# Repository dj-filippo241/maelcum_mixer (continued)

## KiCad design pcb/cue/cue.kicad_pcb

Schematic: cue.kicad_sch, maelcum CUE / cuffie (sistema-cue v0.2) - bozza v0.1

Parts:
C1, C4: 220u 35V; CP_Radial_D8.0mm_P3.50mm
C2, C5: 10u 35V; CP_Radial_D5.0mm_P2.00mm
C3, C6: 1000u 25V; CP_Radial_D10.0mm_P5.00mm
C7, C12: 47u 35V; CP_Radial_D6.3mm_P2.50mm
C8, C11, C13, C16: 10u 25V; C_1206_3216Metric
C9, C10, C14, C15: 4u7 25V; C_1206_3216Metric
C17, C18, C21, C22: 10p C0G; C_0805_2012Metric
C19, C20, C23, C24, C25, C26, C27, C28, C31, C32, C33, C34, C37, C38, C40, C42: 100n; C_0805_2012Metric
C29, C35: 330p C0G; C_0805_2012Metric
C30, C36: 1u film; C_Rect_L7.2mm_W3.5mm_P5.00mm_FKS2_FKP2_MKS2_MKP2
C39: 47u 10V; CP_Radial_D5.0mm_P2.00mm
C41: 2u2 X7R; C_1206_3216Metric
D1, D3, D5: 1N4148W; D_SOD-123
D2, D4: S1G; D_SMA
D6, D7, D8: BAT54W; SOT-323_SC-70
FB1, FB2: ferrite 600R 2A; L_1206_3216Metric
FB3, FB4: ferrite 600R; L_1206_3216Metric
H1, H2: CHASSIS; MountingHole_3.2mm_M3_Pad
J1: C96 maschio; DIN41612_C_3x32_Male_Horizontal_THT
J2: 2x7 cavo piatto; PinHeader_2x07_P2.54mm_Vertical
J3: 2x3 cavo; PinHeader_2x03_P2.54mm_Vertical
K1, K2: G6K-2F DC5; Relay_DPDT_Omron_G6K-2F
Q1, Q6, Q8, Q13: BC847B; SOT-23
Q2, Q3, Q9, Q10: BF245B; TO-92_Inline_Wide
Q4, Q11: MJE340; TO-126-3_Vertical
Q5, Q12: MJE350; TO-126-3_Vertical
Q7, Q14: BC857B; SOT-23
Q15: AO3400A; SOT-23
R1, R3, R5, R8: 120 1%; R_0805_2012Metric
R2, R4: 1k62 1%; R_0805_2012Metric
R6, R9: 1k47 1%; R_0805_2012Metric
R7, R10: 150k 0.1%; R_0805_2012Metric
R11, R12, R13, R14, R15, R16, R17, R18, R19, R20: 10k 0.1%; R_0805_2012Metric
R21, R22, R23, R24: 20k 0.1%; R_0805_2012Metric
R25, R26, R27, R40: 1M; R_0805_2012Metric
R28, R41: 470 1%; R_0805_2012Metric
R29, R30, R31, R42, R43, R44: 1k 1%; R_0805_2012Metric
R32, R33, R45, R46: 22; R_0805_2012Metric
R34, R35, R47, R48: 6.8 1%; R_1206_3216Metric
R36, R37, R49, R50, R53: 100; R_0805_2012Metric
R38, R39, R51, R52: 10 2W; R_Axial_DIN0414_L11.9mm_D4.5mm_P15.24mm_Horizontal
R54: 0; R_1206_3216Metric
R55: 1k; R_0805_2012Metric
R56, R58: 160k 1%; R_0805_2012Metric
R57: 27k4 1%; R_0805_2012Metric
R59: 22k6 1%; R_0805_2012Metric
R60: 15k 1%; R_0805_2012Metric
R61, R62, R64: 10k 1%; R_0805_2012Metric
R63: 120k 1%; R_0805_2012Metric
R65: 140k 1%; R_0805_2012Metric
R66, R68: 10k; R_0805_2012Metric
R67: 1M2 1%; R_0805_2012Metric
RV1, RV2: 500; Potentiometer_Bourns_3266W_Vertical
U1, U2, U3, U4, U8: OPA1612AIDR; SOIC-8_3.9x4.9mm_P1.27mm
U5: TL431; SOT-23
U6, U7: LM339; SOIC-14_3.9x8.7mm_P1.27mm
U40: LM317; TO-220-3_Vertical
U41: LM337; TO-220-3_Vertical
U42: LM317; SOT-223-3_TabPin2
U43: LM337; SOT-223-3_TabPin2
U44: LT3045EMSE; MSOP-12-1EP_3x4.039mm_P0.65mm_EP1.651x2.845mm
U45: LT3094EMSE; MSOP-12-1EP_3x4.039mm_P0.65mm_EP1.651x2.845mm

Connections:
+5V: C39.1, C40.1, C42.1, D5.1 (K), J1.a21, J1.a22, K1.1, K2.1, R55.1, R66.2, R68.2, U6.3 (V+), U7.3 (V+)
+15LN: C11.1, C19.1, C23.1, C25.1, U1.8 (V+), U2.8 (V+), U3.8 (V+), U44.10 (OUTS), U44.11 (OUT), U44.12 (OUT)
+16V5: C8.1, C10.1, R5.1, U42.2 (VO), U44.1 (IN), U44.2 (IN), U44.3 (IN), U44.4 (EN/UV), U44.7 (PGFB)
+18V: C3.1, C27.1, C31.1, C33.1, C37.1, D1.1 (K), D2.2 (A), Q2.3 (D), Q4.2 (C), Q9.3 (D), Q11.2 (C), R1.1, U4.8 (V+), U8.8 (V+), U40.2 (VO)
-15LN: C16.2, C20.2, C24.2, C26.2, U1.4 (V-), U2.4 (V-), U3.4 (V-), U45.10 (OUTS), U45.11 (OUT), U45.12 (OUT)
-16V5: C13.2, C15.2, R8.1, U43.3 (VO), U45.1 (IN), U45.2 (IN), U45.3 (EN/UV), U45.5 (PGFB), U45.13 (IN)
-18V: C6.2, C28.2, C32.2, C34.2, C38.2, D3.2 (A), D4.1 (K), Q3.1 (G), Q3.2 (S), Q5.2 (C), Q10.1 (G), Q10.2 (S), Q12.2 (C), R3.1, U4.4 (V-), U8.4 (V-), U41.3 (VO)
ADJ16+: R5.2, R6.1, U42.1 (ADJ)
ADJ16-: R8.2, R9.1, U43.1 (ADJ)
ADJ18+: C2.1, D1.2 (A), R1.2, R2.1, U40.1 (ADJ)
ADJ18-: C5.2, D3.1 (K), R3.2, R4.1, U41.1 (ADJ)
AGND: C1.2, C2.2, C3.2, C4.1, C5.1, C6.1, C7.2, C8.2, C9.2, C10.2, C11.2, C12.1, C13.1, C14.1, C15.1, C16.1, C19.2, C20.1, C23.2, C24.1, C25.2, C26.1, C27.2, C28.1, C31.2, C32.1, C33.2, C34.1, C37.2, C38.1, J1.a13, J1.a14, J1.a15, J1.a16, J1.a17, J1.a18, J1.a19, J1.a20, J1.b3, J1.b6, J1.b9, J1.b12, J1.b15, J2.2, J2.6, J2.9, J2.13, R2.2, R4.2, R6.2, R7.2, R9.2, R10.2, R25.2, R26.2, R27.2, R40.2, R54.2, U1.3 (+), U1.5 (+), U2.3 (+), U2.5 (+), U4.5 (+), U8.5 (+), U44.6 (ILIM), U44.9 (GND), U44.13 (GND), U45.6 (ILIM), U45.9 (GND)
BLB_L: J2.5, U3.1, U3.2 (-)
BLB_R: J2.12, U3.6 (-), U3.7
BLN_L: Q6.1 (B), R36.2
BLN_R: Q13.1 (B), R49.2
BLP_L: Q7.1 (B), R37.2
BLP_R: Q14.1 (B), R50.2
BL_L: J2.4, R25.1, U3.3 (+)
BL_R: J2.11, R26.1, U3.5 (+)
BN_L: Q4.3 (B), R32.2
BN_R: Q11.3 (B), R45.2
BP_L: Q5.3 (B), R33.2
BP_R: Q12.3 (B), R46.2
CHASSIS: H1.1, H2.1, J1.a25, J1.a26
CS_L: C17.2, J2.1, R15.2, U1.1
CS_R: C18.2, J2.8, R20.2, U1.7
CT: C41.1, D8.1 (A), R67.2, U7.9 (+)
CTRL_GND: C39.2, C40.2, C41.2, C42.2, D6.1 (A), D7.1 (A), J1.a23, J1.a24, J1.c16, J1.c20, J1.c24, J1.c28, Q15.2 (S), R57.2, R59.2, R61.2, U5.3 (A), U6.12 (V-), U7.5 (+), U7.7 (+), U7.11 (+), U7.12 (V-)
CUE1_L: J1.b1, R11.1
CUE1_R: J1.b2, R16.1
CUE2_L: J1.b4, R12.1
CUE2_R: J1.b5, R17.1
CUE3_L: J1.b7, R13.1
CUE3_R: J1.b8, R18.1
CUE4_L: J1.b10, R14.1
CUE4_R: J1.b11, R19.1
D22: R56.2, R57.1, U6.7 (+)
D27: R58.2, R59.1, U6.5 (+)
EN_L: Q4.1 (E), R34.1, R36.1
EN_R: Q11.1 (E), R47.1, R49.1
EP_L: Q5.1 (E), R35.1, R37.1
EP_R: Q12.1 (E), R48.1, R50.1
FB_L: C29.2, R28.2, U4.2 (-)
FB_R: C35.2, R41.2, U8.2 (-)
HP1_R: J3.3, K1.5
HP1_T: J3.1, K1.4
HP2_R: J3.6, K2.5
HP2_T: J3.4, K2.4
HPG: J3.2, J3.5, R54.1
KD: D5.2 (A), K1.8, K2.8, Q15.3 (D)
KG: Q15.1 (G), R53.2
KG0: R53.1, R68.1, U7.14
LV_L: J2.7, R27.1, U4.3 (+)
LV_R: J2.14, R40.1, U8.3 (+)
MB_L: C21.2, J2.3, R22.2, U2.1
MB_R: C22.2, J2.10, R24.2, U2.7
MON_L: J1.b13, R21.1
MON_R: J1.b14, R23.1
N22: D6.3 (K), R62.2, R63.1, U6.8 (-)
N27: D7.3 (K), R64.2, R65.1, U6.10 (-)
NB_L: C30.2, Q1.2 (E), Q3.3 (D), Q7.3 (C), R29.2, R31.2, R33.1
NB_R: C36.2, Q8.2 (E), Q10.3 (D), Q14.3 (C), R42.2, R44.2, R46.1
NMB_L: C21.1, R21.2, R22.1, U2.2 (-)
NMB_R: C22.1, R23.2, R24.1, U2.6 (-)
NS_L: C17.1, R11.2, R12.2, R13.2, R14.2, R15.1, U1.2 (-)
NS_R: C18.1, R16.2, R17.2, R18.2, R19.2, R20.1, U1.6 (-)
NU_L: U4.6 (-), U4.7
NU_R: U8.6 (-), U8.7
OUTA_L: Q6.2 (E), Q7.2 (E), R28.1, R34.2, R35.2, R38.1, R39.1
OUTA_R: Q13.2 (E), Q14.2 (E), R41.1, R47.2, R48.2, R51.1, R52.1
PB_L: C30.1, Q1.3 (C), Q2.1 (G), Q2.2 (S), Q6.3 (C), R30.1, R32.1
PB_R: C36.1, Q8.3 (C), Q9.1 (G), Q9.2 (S), Q13.3 (C), R43.1, R45.1
RAW+22: FB3.1, J1.a5, J1.a6, R56.1
RAW+27: FB1.1, J1.a1, J1.a2, R58.1
RAW-22: FB4.1, J1.a7, J1.a8, R63.2
RAW-27: FB2.1, J1.a3, J1.a4, R65.2
ROK: D8.3 (K), R66.1, R67.1, U6.1, U6.2, U6.13, U6.14
RS1_L: K1.3, R38.2
RS1_R: K1.6, R51.2
RS2_L: K2.3, R39.2
RS2_R: K2.6, R52.2
RT_L: R30.2, RV1.1
RT_R: R43.2, RV2.1
SETN: C14.2, R10.1, U45.8 (SET)
SETP: C9.1, R7.1, U44.8 (SET)
TAP_L: Q1.1 (B), R31.1, RV1.2, RV1.3
TAP_R: Q8.1 (B), R44.1, RV2.2, RV2.3
THN: R60.2, R61.1, U6.9 (+), U6.11 (+)
UO_L: C29.1, R29.1, U4.1
UO_R: C35.1, R42.1, U8.1
V22F+: C7.1, FB3.2, U42.3 (VI)
V22F-: C12.2, FB4.2, U43.2 (VI)
V27F+: C1.1, D2.1 (K), FB1.2, U40.3 (VI)
V27F-: C4.2, D4.2 (A), FB2.2, U41.2 (VI)
VREF: R55.2, R60.1, R62.1, R64.1, U5.1 (K), U5.2 (REF), U6.4 (-), U6.6 (-), U7.4 (-), U7.6 (-), U7.8 (-), U7.10 (-)

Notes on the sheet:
BACKPLANE C96 (classe CUE: slot 1-4 = CUE1-4 in, slot 5 = MON in)
ALIMENTAZIONE +18 audio (LM317 dal raw +27, bulk 1000 uF)
ALIMENTAZIONE -18 audio (LM337 dal raw -27, bulk 1000 uF)
ALIMENTAZIONE +15 LN (LM317 a +16,5 dal raw +22, poi LT3045)
ALIMENTAZIONE -15 LN (LM337 a -16,5 dal raw -22, poi LT3094)
[A] CUE SUMMING L/R (massa virtuale, Rf 10k, -1) e [B] MON (invertente 20k/20k, F4)
[C2] buffer fra BLEND e LEVEL (NOTA: tiene la law del blend esatta)
[E] AMPLI CUFFIA L (OPA1612 + diamond MJE340/350, v0.2)
[F] RSERIE L (10 ohm 2 W, una per jack)
[E] AMPLI CUFFIA R (OPA1612 + diamond MJE340/350, v0.2)
[F] RSERIE R (10 ohm 2 W, una per jack)
[F] RELE' delle cuffie (G6K-2F, 5 V, 237 ohm; eccitati = suono; failsafe)
[G] PROTEZIONE: finestre sui raw +-22 e +-27, timer 1,8 s (il CUE non ascolta c9)
CAVI verso la scheda comandi: J2 pot, J3 cuffie

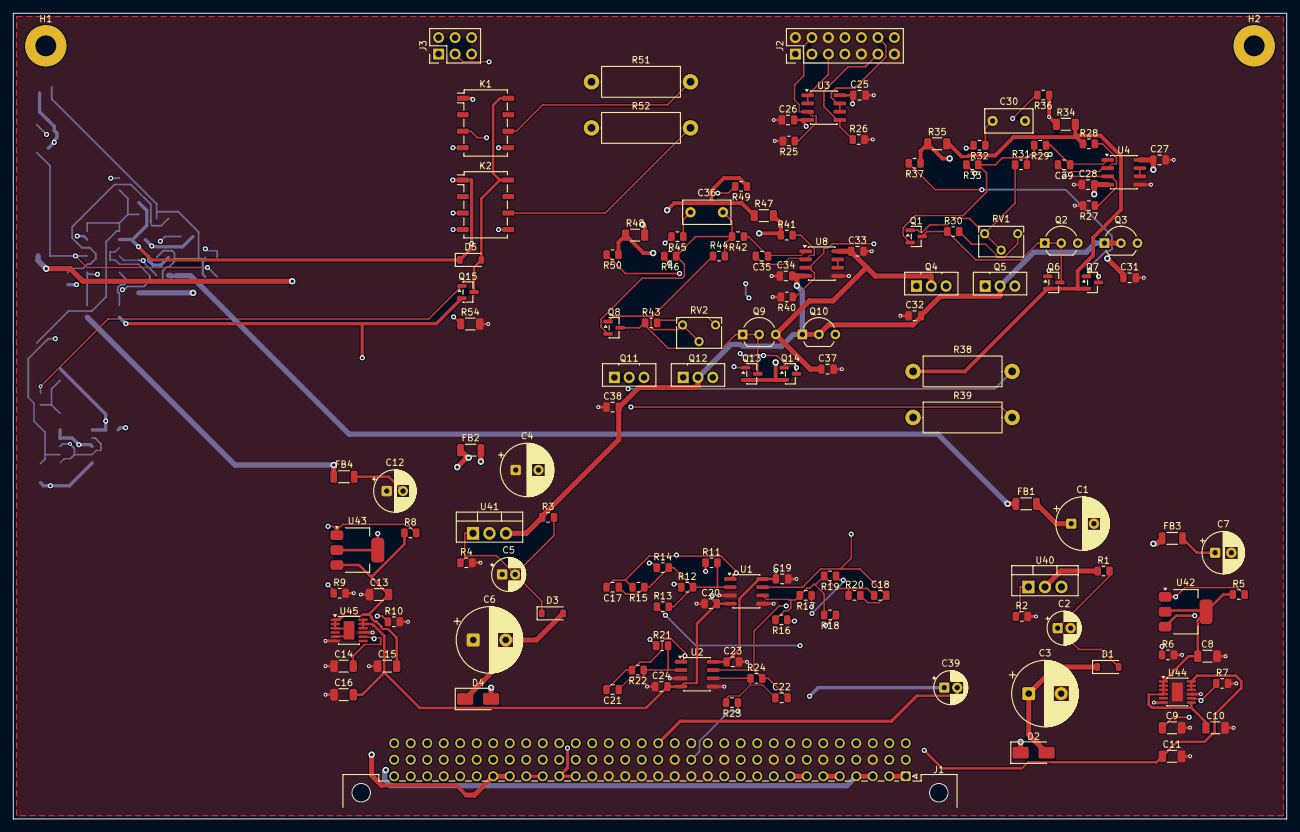
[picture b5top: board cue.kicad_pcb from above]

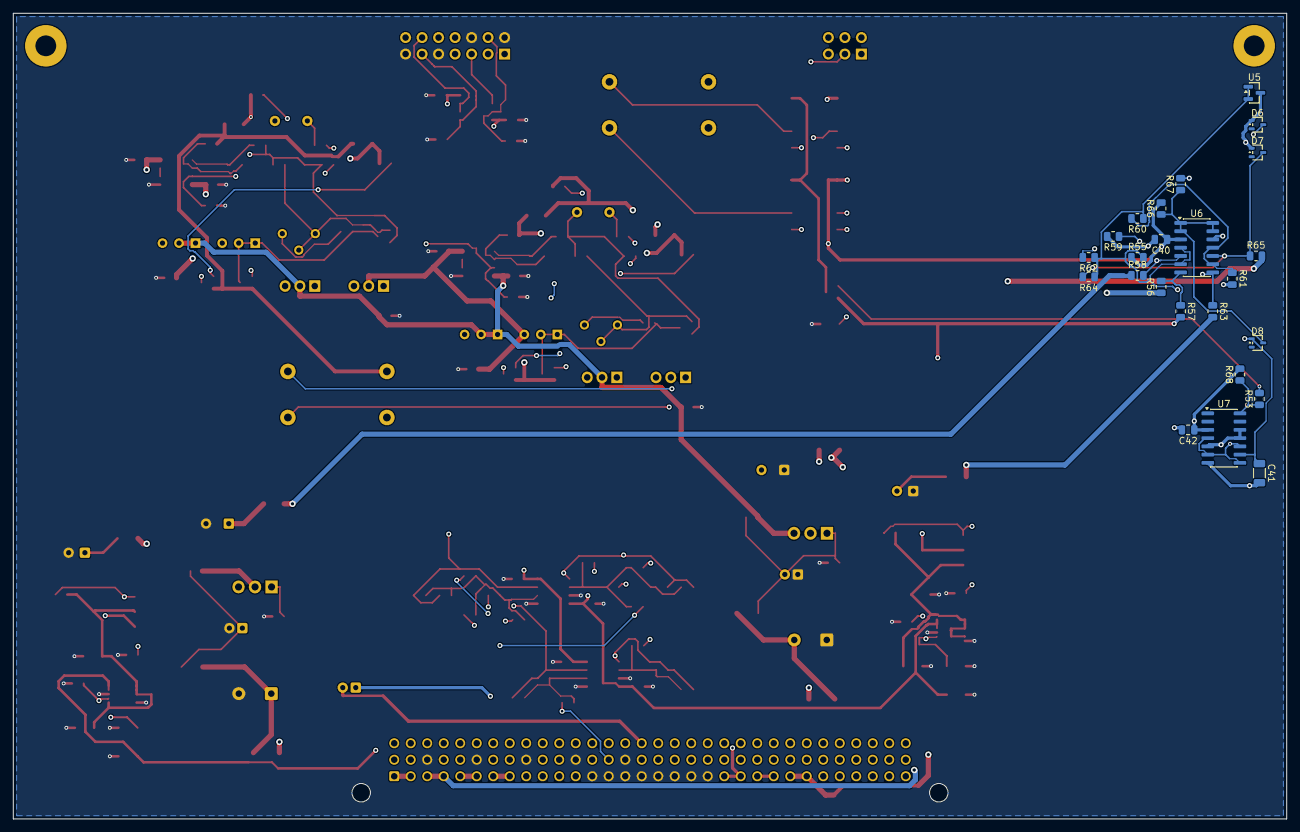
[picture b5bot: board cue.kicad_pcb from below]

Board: 4 copper layers, 196.0 x 124.0 mm, 160 parts (24 on the bottom side), 96 nets.

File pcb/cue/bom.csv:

quantita;valore;impronta;riferimenti;nota
2;220u 35V;CP_Radial_D8.0mm_P3.50mm;C1 C4;
3;4u7 25V;C_1206_3216Metric;C10 C14 C15;
2;10p C0G;C_0805_2012Metric;C17 C18;NOTA: come i ricevitori dei bus (Cf 10 pF)
14;100n;C_0805_2012Metric;C19 C20 C23 C24 C25 C26 C27 C28 C32 C33 C34 C38 C40 C42;
2;10u 35V;CP_Radial_D5.0mm_P2.00mm;C2 C5;
2;10p C0G;C_0805_2012Metric;C21 C22;
2;330p C0G;C_0805_2012Metric;C29 C35;Cf: incrocio dell'anello esterno ~1 MHz
1;1000u 25V;CP_Radial_D10.0mm_P5.00mm;C3;bulk locale dei finali (§5)
2;1u film;C_Rect_L7.2mm_W3.5mm_P5.00mm_FKS2_FKP2_MKS2_MKP2;C30 C36;Cb, film (WIMA MKS2 o simile)
2;100n;C_0805_2012Metric;C31 C37;ai collettori dei finali
1;47u 10V;CP_Radial_D5.0mm_P2.00mm;C39;riserva dei relè
1;2u2 X7R;C_1206_3216Metric;C41;
1;1000u 25V;CP_Radial_D10.0mm_P5.00mm;C6;
2;47u 35V;CP_Radial_D6.3mm_P2.50mm;C7 C12;
4;10u 25V;C_1206_3216Metric;C8 C11 C13 C16;
1;4u7 25V;C_1206_3216Metric;C9;rumore del riferimento (datasheet: 4,7 uF)
1;1N4148W;D_SOD-123;D1;scarica Cadj
1;S1G;D_SMA;D2;protezione inversa (bulk 1000 uF)
1;1N4148W;D_SOD-123;D3;
1;S1G;D_SMA;D4;
1;1N4148W;D_SOD-123;D5;scarica delle bobine
2;BAT54W;SOT-323_SC-70;D6 D7;+5V spento e raw negativo presente: il nodo non scende sotto -0,3 V
1;BAT54W;SOT-323_SC-70;D8;scarica CT in ~1 ms: i relè aprono subito al calo di un raw
2;ferrite 600R 2A;L_1206_3216Metric;FB1 FB2;
2;ferrite 600R;L_1206_3216Metric;FB3 FB4;
1;C96 maschio;DIN41612_C_3x32_Male_Horizontal_THT;J1;DIN 41612 C 3x32, angolo retto; c9 libero per scelta (sistema-cue §6)
1;2x7 cavo piatto;PinHeader_2x07_P2.54mm_Vertical;J2;pot BLEND e LEVEL (stesso ordine in cue-comandi.py)
1;2x3 cavo;PinHeader_2x03_P2.54mm_Vertical;J3;NOTA: due jack cuffie sulla scheda comandi; HPG = ritorno, unito ad AGND solo qui
1;G6K-2F DC5;Relay_DPDT_Omron_G6K-2F;K1;PHONES 1: L sulla punta, R sull'anello
1;G6K-2F DC5;Relay_DPDT_Omron_G6K-2F;K2;PHONES 2: L sulla punta, R sull'anello
2;BC847B;SOT-23;Q1 Q8;moltiplicatore di Vbe: vicino ai finali per l'inseguimento termico (§12)
1;AO3400A;SOT-23;Q15;driver dei relè, logic level
2;BF245B;TO-92_Inline_Wide;Q2 Q9;CRD ~8 mA: Idss da selezionare (BF245B 6-15 mA)
2;BF245B;TO-92_Inline_Wide;Q3 Q10;CRD ~8 mA
2;MJE340;TO-126-3_Vertical;Q4 Q11;finale +: 0,35 W a riposo, ~3 W in corto; rame >= 4 cm2 (§5)
2;MJE350;TO-126-3_Vertical;Q5 Q12;finale -; rame >= 4 cm2
2;BC847B;SOT-23;Q6 Q13;limitatore +
2;BC857B;SOT-23;Q7 Q14;limitatore -
4;120 1%;R_0805_2012Metric;R1 R3 R5 R8;
8;10k 0.1%;R_0805_2012Metric;R11 R12 R13 R14 R16 R17 R18 R19;NOTA: iniezione 10k qui; il canale esce con 47 ohm dopo lo switch (canale.py)
2;10k 0.1%;R_0805_2012Metric;R15 R20;
1;1k62 1%;R_0805_2012Metric;R2;18,1 V (come master-uscita.py)
2;20k 0.1%;R_0805_2012Metric;R21 R23;REV 2026-11-03 (F4): buffer MON invertente
2;20k 0.1%;R_0805_2012Metric;R22 R24;
2;1M;R_0805_2012Metric;R25 R26;tiene l'ingresso a massa a cavo staccato
2;1M;R_0805_2012Metric;R27 R40;NOTA: tiene l'ingresso a massa a cavo staccato (il cursore del LEVEL basta in uso)
2;470 1%;R_0805_2012Metric;R28 R41;Rf: retroazione DC da OUTA, prima della Rserie
2;1k 1%;R_0805_2012Metric;R29 R42;Rdrv: isola l'op-amp e fissa la corrente che i limitatori vincono
4;1k 1%;R_0805_2012Metric;R30 R31 R43 R44;
2;22;R_0805_2012Metric;R32 R45;base stopper
2;22;R_0805_2012Metric;R33 R46;
2;6.8 1%;R_1206_3216Metric;R34 R47;Re: stabilità termica e senso della corrente
2;6.8 1%;R_1206_3216Metric;R35 R48;
5;100;R_0805_2012Metric;R36 R37 R49 R50 R53;
2;10 2W;R_Axial_DIN0414_L11.9mm_D4.5mm_P15.24mm_Horizontal;R38 R51;Rserie del jack 1: isola i due jack, stabilità sul carico
2;10 2W;R_Axial_DIN0414_L11.9mm_D4.5mm_P15.24mm_Horizontal;R39 R52;Rserie del jack 2: isola i due jack, stabilità sul carico
1;1k62 1%;R_0805_2012Metric;R4;
1;0;R_1206_3216Metric;R54;NOTA: ritorno delle cuffie (J3) unito ad AGND qui, vicino all'ampli
1;1k;R_0805_2012Metric;R55;
1;160k 1%;R_0805_2012Metric;R56;+22 < 17,1 V = muto (§6)
1;27k4 1%;R_0805_2012Metric;R57;
1;160k 1%;R_0805_2012Metric;R58;+27 < 20,2 V = muto (§6)
1;22k6 1%;R_0805_2012Metric;R59;
1;1k47 1%;R_0805_2012Metric;R6;16,6 V
1;15k 1%;R_0805_2012Metric;R60;
1;10k 1%;R_0805_2012Metric;R61;
1;10k 1%;R_0805_2012Metric;R62;-22 > -17,0 V = muto
1;120k 1%;R_0805_2012Metric;R63;
1;10k 1%;R_0805_2012Metric;R64;-27 > -20,0 V = muto
1;140k 1%;R_0805_2012Metric;R65;
1;10k;R_0805_2012Metric;R66;ROK alto = quattro raw dentro la finestra
1;1M2 1%;R_0805_2012Metric;R67;RT: accensione ~1,8 s (1,5-2 s, §6)
1;10k;R_0805_2012Metric;R68;KG0 alto = cuffie collegate
2;150k 0.1%;R_0805_2012Metric;R7 R10;
1;1k47 1%;R_0805_2012Metric;R9;
2;500;Potentiometer_Bourns_3266W_Vertical;RV1 RV2;trimmer del riposo: 210 ohm = 20 mA (si tara a banco, §12)
1;OPA1612AIDR;SOIC-8_3.9x4.9mm_P1.27mm;U1;[A] somma dei cue
1;OPA1612AIDR;SOIC-8_3.9x4.9mm_P1.27mm;U2;[B] MON dal master, -1
1;OPA1612AIDR;SOIC-8_3.9x4.9mm_P1.27mm;U3;inseguitori: il LEVEL da 10k non carica il cursore del BLEND (centro -6 dB per parte)
2;OPA1612AIDR;SOIC-8_3.9x4.9mm_P1.27mm;U4 U8;gain +1: retroazione da OUTA (Rf 470), compensazione Cf 330p; sezione B libera
1;LM317;TO-220-3_Vertical;U40;+18 V dell'ampli cuffia: 61 mA a riposo, ~0,55 W
1;LM337;TO-220-3_Vertical;U41;
1;LM317;SOT-223-3_TabPin2;U42;pre-regolatore (§2: +-16,5); ~25 mA
1;LM337;SOT-223-3_TabPin2;U43;
1;LT3045EMSE;MSOP-12-1EP_3x4.039mm_P0.65mm_EP1.651x2.845mm;U44;EN/UV a IN; ILIM a massa; PG libero; PGFB a IN (come master-segnale.py)
1;LT3094EMSE;MSOP-12-1EP_3x4.039mm_P0.65mm_EP1.651x2.845mm;U45;EN/UV a IN; PG libero; PGFB a IN; ILIM a massa; VIOC libero
1;TL431;SOT-23;U5;2,495 V
1;LM339;SOIC-14_3.9x8.7mm_P1.27mm;U6;finestre dei quattro raw (uscite in OR)
1;LM339;SOIC-14_3.9x8.7mm_P1.27mm;U7;timer dei relè

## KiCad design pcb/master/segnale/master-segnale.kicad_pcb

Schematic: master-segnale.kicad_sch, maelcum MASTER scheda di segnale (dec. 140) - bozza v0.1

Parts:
C1, C2: 220u 35V; CP_Radial_D8.0mm_P3.50mm
C3, C7: 10u 35V; CP_Radial_D5.0mm_P2.00mm
C4, C8: 47u 35V; CP_Radial_D6.3mm_P2.50mm
C5, C9: 470u 25V; CP_Radial_D8.0mm_P3.50mm
C6, C10: 100u 25V; CP_Radial_D6.3mm_P2.50mm
C11, C12, C14, C15: 4u7 25V; C_1206_3216Metric
C13, C16: 10u 25V; C_1206_3216Metric
C17: 1u; C_1206_3216Metric
C18, C19, C20, C21, C25, C26, C27, C28, C30, C31, C33, C34, C35, C36, C37, C38, C39, C40, C41, C42, C43, C44, C45, C46, C47, C48, C49, C50, C53, C54, C55, C56, C57, C58, C59, C60, C63, C64, C65, C66, C67, C68, C71, C72, C73, C74, C77, C78, C79, C80, C81, C82: 100n; C_0805_2012Metric
C22, C23: 10p C0G; C_0805_2012Metric
C24, C69, C75: 47p C0G; C_0805_2012Metric
C29, C51, C52, C61, C62: 22p C0G; C_0805_2012Metric
C32: 100n C0G; C_0805_2012Metric
C70, C76: 100n C0G; C_1206_3216Metric
D1, D3, D6, D7, D8, D9, D10, D11, D12, D13, D14: 1N4148W; D_SOD-123
D2, D4: S1G; D_SMA
D5: LM4040-5.0; SOT-23
FB1, FB2: ferrite 600R; L_1206_3216Metric
H1, H2: CHASSIS; MountingHole_3.2mm_M3_Pad
J1: C96 maschio; DIN41612_C_3x32_Male_Horizontal_THT
J2: 2x7 cavo piatto; PinHeader_2x07_P2.54mm_Vertical
J3: 2x10 cavo piatto; PinHeader_2x10_P2.54mm_Vertical
JP1, JP4: 0 dB; SolderJumper-2_P1.3mm_Bridged_RoundedPad1.0x1.5mm
JP2, JP5: -10 dB; SolderJumper-2_P1.3mm_Open_RoundedPad1.0x1.5mm
JP3, JP6: -20 dB; SolderJumper-2_P1.3mm_Open_RoundedPad1.0x1.5mm
Q40: BD139; TO-126-3_Vertical
Q41: BD140; TO-126-3_Vertical
R1, R4: 120 1%; R_0805_2012Metric
R2, R5: 1k72 1%; R_0805_2012Metric
R3, R6, R126, R130: 1k; R_0805_2012Metric
R7, R8: 150k 0.1%; R_0805_2012Metric
R9: 1k5; R_0805_2012Metric
R10, R11, R30, R32, R34, R87, R113, R124, R128, R132, R134: 10k 0.1%; R_0805_2012Metric
R12, R13, R14, R15, R16, R19, R20, R21, R22, R23, R24, R27, R28, R29, R31, R33, R35, R39, R40, R41, R42, R43, R44, R45, R46, R67, R71, R75, R76, R96, R100, R104, R105: 20k 0.1%; R_0805_2012Metric
R17, R18, R25, R26: 0; R_0805_2012Metric
R36, R68, R72, R97, R101: 6k19; R_0805_2012Metric
R37, R69, R73, R98, R102: 150k; R_0805_2012Metric
R38, R70, R74, R99, R103: 51; R_0805_2012Metric
R47, R48: 10k; R_0805_2012Metric
R49: 10k2 0.1%; R_0805_2012Metric
R50: 7k5 0.1%; R_0805_2012Metric
R51, R91, R117: 18k2 0.1%; R_0805_2012Metric
R52, R92, R94, R118, R120: 1k 0.1%; R_0805_2012Metric
R53, R54, R63, R64, R65, R66, R122, R123: 47; R_0805_2012Metric
R55, R56, R90, R116: 100k; R_0805_2012Metric
R57, R60: 6k81 0.1%; R_0805_2012Metric
R58, R61: 3k16 0.1%; R_0805_2012Metric
R59, R62: 757 0.1%; R_0805_2012Metric
R77, R107: 68.1k 0.1%; R_0805_2012Metric
R78: 137k 0.1%; R_0805_2012Metric
R79: 1.91k 0.1%; R_0805_2012Metric
R80, R84: 2.43k 0.1%; R_0805_2012Metric
R81: 16.9k 0.1%; R_0805_2012Metric
R82, R110: 38.3k 0.1%; R_0805_2012Metric
R83: 1.82k 0.1%; R_0805_2012Metric
R85: 1.96k 0.1%; R_0805_2012Metric
R86: 2.61k 0.1%; R_0805_2012Metric
R88, R114: 9k76 0.1%; R_0805_2012Metric
R89, R115: 18k7 0.1%; R_0805_2012Metric
R93, R119: 17k4 0.1%; R_0805_2012Metric
R95, R121: 2M7; R_0805_2012Metric
R106: 43.2k 0.1%; R_0805_2012Metric
R108: 357k 0.1%; R_0805_2012Metric
R109: 20.0k 0.1%; R_0805_2012Metric
R111: 976 0.1%; R_0805_2012Metric
R112: 1.33k 0.1%; R_0805_2012Metric
R125, R129: 4k02 0.1%; R_0805_2012Metric
R127, R131: 3M; R_0805_2012Metric
R133: 5k 0.1%; R_0805_2012Metric
R135: 4k64 0.1%; R_0805_2012Metric
RV1, RV2, RV3, RV5, RV6, RV7, RV9: 50k; Potentiometer_Bourns_3266W_Vertical
RV4, RV8: 2k; Potentiometer_Bourns_3266W_Vertical
U1, U2, U3, U4, U5, U6, U7, U8, U10, U11, U14, U15, U16, U19, U20, U21, U22, U23, U24, U25, U30: OPA1612AIDR; SOIC-8_3.9x4.9mm_P1.27mm
U9, U12, U13, U17, U18: V2181L; SOIC-8_3.9x4.9mm_P1.27mm
U40: LM317; TO-220-3_Vertical
U41: LM337; TO-220-3_Vertical
U42: LT3045EMSE; MSOP-12-1EP_3x4.039mm_P0.65mm_EP1.651x2.845mm
U43: LT3094EMSE; MSOP-12-1EP_3x4.039mm_P0.65mm_EP1.651x2.845mm

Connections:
+15LN: C13.1, C18.1, C20.1, C25.1, C30.1, C33.1, C35.1, C37.1, C43.1, C45.1, C55.1, C65.1, C71.1, C73.1, C77.1, C79.1, C81.1, R9.1, R132.1, RV1.1, RV2.1, RV3.1, RV5.1, RV6.1, RV7.1, RV9.1, U1.8 (V+), U2.8 (V+), U3.8 (V+), U4.8 (V+), U5.8 (V+), U6.8 (V+), U10.8 (V+), U11.8 (V+), U15.8 (V+), U16.8 (V+), U21.8 (V+), U22.8 (V+), U23.8 (V+), U24.8 (V+), U25.8 (V+), U30.8 (V+), U42.10 (OUTS), U42.11 (OUT), U42.12 (OUT)
+18V: C6.1, C12.1, C27.1, C39.1, C41.1, C47.1, C49.1, C53.1, C57.1, C59.1, C63.1, C67.1, Q40.1 (E), U7.8 (V+), U8.8 (V+), U9.7 (V+), U12.7 (V+), U13.7 (V+), U14.8 (V+), U17.7 (V+), U18.7 (V+), U19.8 (V+), U20.8 (V+), U42.1 (IN), U42.2 (IN), U42.3 (IN), U42.4 (EN/UV), U42.7 (PGFB)
+REF5: J3.5, R10.1, U30.1, U30.2 (-)
-15LN: C16.2, C19.2, C21.2, C26.2, C31.2, C34.2, C36.2, C38.2, C44.2, C46.2, C56.2, C66.2, C72.2, C74.2, C78.2, C80.2, C82.2, RV1.3, RV2.3, RV3.3, RV5.3, RV6.3, RV7.3, RV9.3, U1.4 (V-), U2.4 (V-), U3.4 (V-), U4.4 (V-), U5.4 (V-), U6.4 (V-), U10.4 (V-), U11.4 (V-), U15.4 (V-), U16.4 (V-), U21.4 (V-), U22.4 (V-), U23.4 (V-), U24.4 (V-), U25.4 (V-), U30.4 (V-), U43.10 (OUTS), U43.11 (OUT), U43.12 (OUT)
-18V: C10.2, C15.2, C28.2, C40.2, C42.2, C48.2, C50.2, C54.2, C58.2, C60.2, C64.2, C68.2, Q41.1 (E), R36.2, R68.2, R72.2, R97.2, R101.2, U7.4 (V-), U8.4 (V-), U14.4 (V-), U19.4 (V-), U20.4 (V-), U43.1 (IN), U43.2 (IN), U43.3 (EN/UV), U43.5 (PGFB), U43.13 (IN)
-REF5: R11.2, R78.1, R80.2, R82.2, R84.2, R86.2, R108.2, R110.2, R112.2, U30.7
ADJ+: C3.1, D1.2 (A), R1.2, R2.1, U40.1 (ADJ)
ADJ-: C7.2, D3.1 (K), R4.2, R5.1, U41.1 (ADJ)
AGND: C1.2, C2.1, C3.2, C4.2, C5.2, C6.2, C7.1, C8.1, C9.1, C10.1, C11.2, C12.2, C13.2, C14.1, C15.1, C16.1, C17.2, C18.2, C19.1, C20.2, C21.1, C25.2, C26.1, C27.2, C28.1, C30.2, C31.1, C32.2, C33.2, C34.1, C35.2, C36.1, C37.2, C38.1, C39.2, C40.1, C41.2, C42.1, C43.2, C44.1, C45.2, C46.1, C47.2, C48.1, C49.2, C50.1, C53.2, C54.1, C55.2, C56.1, C57.2, C58.1, C59.2, C60.1, C63.2, C64.1, C65.2, C66.1, C67.2, C68.1, C70.2, C71.2, C72.1, C73.2, C74.1, C76.2, C77.2, C78.1, C79.2, C80.1, C81.2, C82.1, D5.2 (A), J1.a13, J1.a14, J1.a15, J1.a16, J1.a17, J1.a18, J1.a19, J1.a20, J1.b3, J1.b6, J1.b9, J1.b12, J1.b15, J1.b18, J1.b21, J1.b24, J1.b27, J1.b30, J2.1, J2.3, J2.5, J2.7, J2.9, J2.11, J3.2, J3.4, J3.6, J3.8, J3.10, J3.12, JP2.2 (B), JP3.2 (B), JP5.2 (B), JP6.2 (B), R2.2, R5.2, R7.2, R8.2, R32.2, R38.2, R44.2, R47.2, R50.2, R52.2, R55.2, R56.2, R70.2, R74.2, R90.2, R92.2, R94.2, R99.2, R103.2, R116.2, R118.2, R120.2, R125.2, R127.2, R129.2, R131.2, R133.2, R135.2, U1.3 (+), U1.5 (+), U2.3 (+), U3.3 (+), U3.5 (+), U9.2 (EC+), U9.6 (GND), U12.2 (EC+), U12.6 (GND), U13.2 (EC+), U13.6 (GND), U14.3 (+), U14.5 (+), U15.3 (+), U15.5 (+), U16.3 (+), U16.5 (+), U17.2 (EC+), U17.6 (GND), U18.2 (EC+), U18.6 (GND), U19.3 (+), U19.5 (+), U22.5 (+), U24.5 (+), U30.5 (+), U42.6 (ILIM), U42.9 (GND), U42.13 (GND), U43.6 (ILIM), U43.9 (GND)
BASE+: C5.1, Q40.3 (B), R3.2
BASE-: C9.2, Q41.3 (B), R6.2
BA_L: R67.1, U7.1, U7.2 (-)
BA_R: R71.1, U7.6 (-), U7.7
BB_L: R96.1, U8.1, U8.2 (-)
BB_R: R100.1, U8.6 (-), U8.7
BOOTH_L: C61.2, J2.6, R104.2, U19.1
BOOTH_R: C62.2, J2.8, R105.2, U19.7
CHASSIS: H1.1, H2.1, J1.a25, J1.a26
CLIP_L: J2.13, J3.15
CLIP_R: J2.14, J3.16
CTRL_GND: J1.c16, J1.c20, J1.c24, J1.c28
CVP_B: R115.2, R117.1, R119.1, U16.7
CVP_M: R89.2, R91.1, R93.1, U15.7
D1A_L: D13.2 (A), R126.2
D1A_R: D14.2 (A), R130.2
DOUT_L: C69.1, R126.1, U21.7
DOUT_R: C75.1, R130.1, U23.7
DRVREC_L: R63.1, U10.1, U10.2 (-)
DRVREC_R: R64.1, U10.6 (-), U10.7
ECM_BL: R117.2, R118.1, U17.3 (EC-)
ECM_BR: R120.1, R121.2, RV8.2, RV8.3, U18.3 (EC-)
ECM_ML: R91.2, R92.1, U12.3 (EC-)
ECM_MONO: R51.2, R52.1, U9.3 (EC-)
ECM_MR: R94.1, R95.2, RV4.2, RV4.3, U13.3 (EC-)
HOLD_L: C69.2, C70.1, D13.1 (K), R127.1, U21.6 (-), U22.3 (+)
HOLD_R: C75.2, C76.1, D14.1 (K), R131.1, U23.6 (-), U24.3 (+)
INS_RET_L: J1.b28, R55.1, U6.3 (+)
INS_RET_R: J1.b29, R56.1, U6.5 (+)
INS_SEND_L: J1.b25, R53.2
INS_SEND_R: J1.b26, R54.2
ISD_L: R53.1, U5.1, U5.2 (-)
ISD_R: R54.1, U5.6 (-), U5.7
LO_L: R46.2, U4.1, U5.3 (+)
LO_R: R42.2, U3.7, U5.5 (+)
LT_B: R119.2, RV8.1
LT_M: R93.2, RV4.1
MAST_L: C51.2, J2.2, R75.2, R124.1, U14.1, U20.3 (+)
MAST_R: C52.2, J2.4, R76.2, R128.1, U14.7, U20.5 (+)
MBUF: R49.2, R51.1, U4.7
MET_L: J3.9, U22.1, U22.2 (-)
MET_R: J3.11, U24.1, U24.2 (-)
MFB: R49.1, R50.1, U4.6 (-)
MGB_L: U21.1, U21.2 (-), U21.5 (+)
MGB_R: U23.1, U23.2 (-), U23.5 (+)
MG_L: R124.2, R125.1, U21.3 (+)
MG_R: R128.2, R129.1, U23.3 (+)
MID: C24.2, R30.2, R40.1, R45.1, U2.1
MONB_L: R65.1, U11.1, U11.2 (-)
MONB_R: R66.1, U11.6 (-), U11.7
MONO_SW: J3.7, R47.1, R48.1
MON_OUT_L: J1.b22, R65.2
MON_OUT_R: J1.b23, R66.2
MRC: C32.1, R48.2, U4.5 (+)
MSUM1_L: J1.b1, R12.1
MSUM1_R: J1.b2, R20.1
MSUM2_L: J1.b4, R13.1
MSUM2_R: J1.b5, R21.1
MSUM3_L: J1.b7, R14.1
MSUM3_R: J1.b8, R22.1
MSUM4_L: J1.b10, R15.1
MSUM4_R: J1.b11, R23.1
MSUM5_L: J1.b13, R16.1
MSUM5_R: J1.b14, R24.1
MSUM6_L: J1.b16, R17.1
MSUM6_R: J1.b17, R25.1
MSUM7_L: J1.b19, R18.1
MSUM7_R: J1.b20, R26.1
NIB_L: C61.1, R104.1, U17.8 (OUT), U19.2 (-)
NIB_R: C62.1, R105.1, U18.8 (OUT), U19.6 (-)
NIM_L: C51.1, R75.1, U12.8 (OUT), U14.2 (-)
NIM_R: C52.1, R76.1, U13.8 (OUT), U14.6 (-)
NLO: R40.2, R41.2, R42.1, U3.6 (-)
NM: C24.1, R28.2, R29.2, R30.1, U2.2 (-)
NP_B: R114.2, R115.1, U16.6 (-)
NP_M: R88.2, R89.1, U15.6 (-)
NREF5I: R10.2, R11.1, U30.6 (-)
NSV: C29.1, R39.1, U3.2 (-), U9.8 (OUT)
NS_L: C22.1, R12.2, R13.2, R14.2, R15.2, R16.2, R17.2, R18.2, R19.1, U1.2 (-)
NS_R: C23.1, R20.2, R21.2, R22.2, R23.2, R24.2, R25.2, R26.2, R27.1, U1.6 (-)
NU_L: U22.6 (-), U22.7
NU_R: U24.6 (-), U24.7
OF_B: R121.1, RV9.2
OF_M: R95.1, RV5.2
P10_L: JP2.1 (A), R58.2
P10_R: JP5.1 (A), R61.2
P20_L: JP3.1 (A), R59.2
P20_R: JP6.1 (A), R62.2
PAD_L: JP1.2 (B), R57.2, R58.1, R59.1, U10.3 (+)
PAD_R: JP4.2 (B), R60.2, R61.1, R62.1, U10.5 (+)
POT_B: J3.3, R106.1, R107.1, R109.1, R111.1, R116.1
POT_M: J3.1, R77.1, R79.1, R81.1, R83.1, R85.1, R90.1
PROG_L: JP1.1 (A), R57.1, U6.1, U6.2 (-), U7.3 (+), U8.3 (+), U11.3 (+)
PROG_R: JP4.1 (A), R60.1, U6.6 (-), U6.7, U7.5 (+), U8.5 (+), U11.5 (+)
RAW+27: FB1.1, J1.a1, J1.a2
RAW-27: FB2.1, J1.a3, J1.a4
RDN: R45.2, R46.1, U4.2 (-)
RDP: R43.2, R44.1, U4.3 (+)
REC_L: J2.10, R63.2
REC_R: J2.12, R64.2
REF5K: C17.1, D5.1 (K), R9.2, U30.3 (+)
SDN: R33.2, R34.1, U2.6 (-)
SDP: R31.2, R32.1, U2.5 (+)
SETN: C14.2, R8.1, U43.8 (SET)
SETP: C11.1, R7.1, U42.8 (SET)
SH_B: R113.2, R114.1, U16.1
SH_M: R87.2, R88.1, U15.1
SIDE: R34.2, R35.1, U2.7
SJ_B: D10.1 (K), D11.1 (K), D12.1 (K), R106.2, R113.1, U16.2 (-)
SJ_M: D6.1 (K), D7.1 (K), D8.1 (K), D9.1 (K), R77.2, R78.2, R87.1, U15.2 (-)
SN1_B: D10.2 (A), R107.2, R108.1
SN1_M: D6.2 (A), R79.2, R80.1
SN2_B: D11.2 (A), R109.2, R110.1
SN2_M: D7.2 (A), R81.2, R82.1
SN3_B: D12.2 (A), R111.2, R112.1
SN3_M: D8.2 (A), R83.2, R84.1
SN4_M: D9.2 (A), R85.2, R86.1
SUM_L: C22.2, R19.2, R28.1, R31.1, U1.1
SUM_R: C23.2, R27.2, R29.1, R33.1, U1.7
SV: C29.2, R39.2, R41.1, R43.1, U3.1
SW_u9: R37.1, RV1.2
SW_u12: R69.1, RV2.2
SW_u13: R73.1, RV3.2
SW_u17: R98.1, RV6.2
SW_u18: R102.1, RV7.2
SYM_u9: R37.2, R38.1, U9.4 (SYM)
SYM_u12: R69.2, R70.1, U12.4 (SYM)
SYM_u13: R73.2, R74.1, U13.4 (SYM)
SYM_u17: R98.2, R99.1, U17.4 (SYM)
SYM_u18: R102.2, R103.1, U18.4 (SYM)
V27F+: C1.1, D2.1 (K), FB1.2, U40.3 (VI)
V27F-: C2.2, D4.2 (A), FB2.2, U41.2 (VI)
VEE_u9: R36.1, U9.5 (V-)
VEE_u12: R68.1, U12.5 (V-)
VEE_u13: R72.1, U13.5 (V-)
VEE_u17: R97.1, U17.5 (V-)
VEE_u18: R101.1, U18.5 (V-)
VIE_TAP_L: J1.b31, R122.2
VIE_TAP_R: J1.b32, R123.2
VIN_u9: R35.2, U9.1 (IN)
VIN_u12: R67.2, U12.1 (IN)
VIN_u13: R71.2, U13.1 (IN)
VIN_u17: R96.2, U17.1 (IN)
VIN_u18: R100.2, U18.1 (IN)
VRA0: R132.2, R133.1, U25.3 (+)
VRB0: R134.2, R135.1, U25.5 (+)
VREFA: J3.13, R134.1, U25.1, U25.2 (-)
VREFB: J3.14, U25.6 (-), U25.7
VREG+: C4.1, D1.1 (K), D2.2 (A), Q40.2 (C), R1.1, R3.1, U40.2 (VO)
VREG-: C8.2, D3.2 (A), D4.1 (K), Q41.2 (C), R4.1, R6.1, U41.3 (VO)
VTD_L: R122.1, U20.1, U20.2 (-)
VTD_R: R123.1, U20.6 (-), U20.7

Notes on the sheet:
BACKPLANE C96 (classe MASTER)
ALIMENTAZIONE +-18 (LM317/337 + cap-moltiplicatore), +-15 LN (LT3045/LT3094)
MASTER SUMMING [A2] (invertente, 20k/20k/10p, sum-noise-71A.cir)
MONO [A3] (matrice M/S + VCA su S, mono-ms.cir; resistenze NOTA)
INS_SEND driver + INS_RET buffer (slot 9-10, ponticello JMS sul backplane)
BUFFER [A] [B] [C] [N] (un buffer per uscita, voce 11)
MASTER LEVEL [D]: 2 VCA, shaper (shaper-master.cir), trim di law (vca-trim §3.2)
BOOTH LEVEL [B2]: 2 VCA, shaper del fader (shaper-fader.cir), trim di law
VIE_TAP [V]: driver dopo MASTER LEVEL verso b31-b32
METER [E]: detector di picco L/R (meter-det-03s.cir) e albero dei riferimenti (metering §5)
CONNETTORI: J2 verso la scheda di USCITA, J3 verso la scheda COMANDI

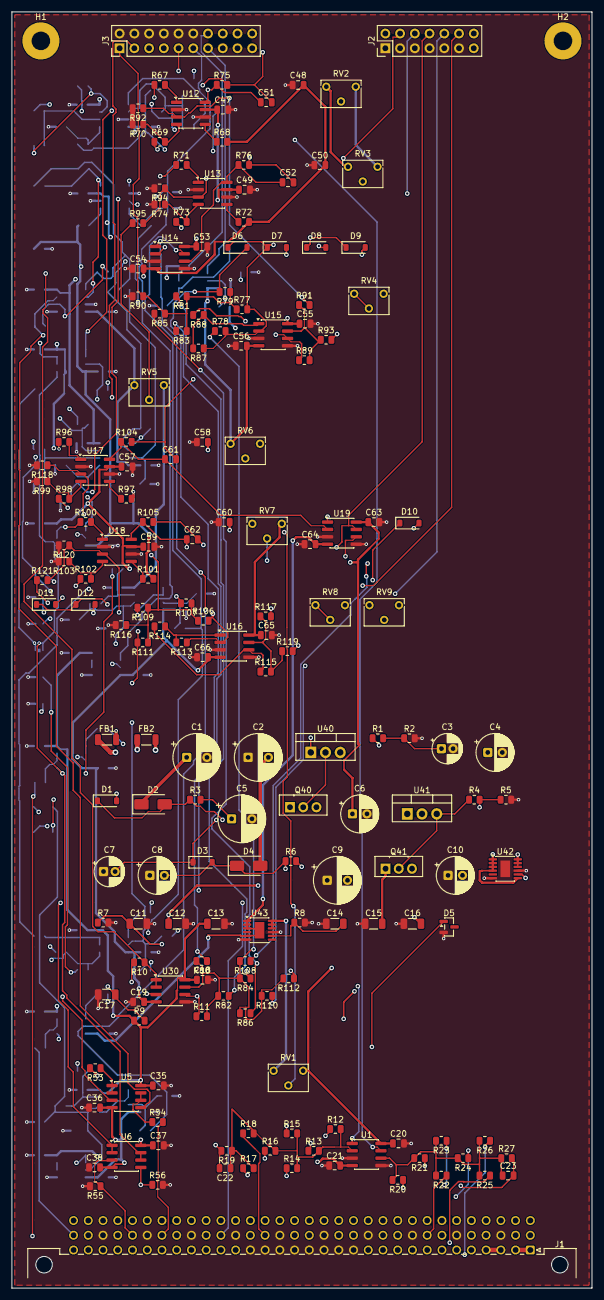
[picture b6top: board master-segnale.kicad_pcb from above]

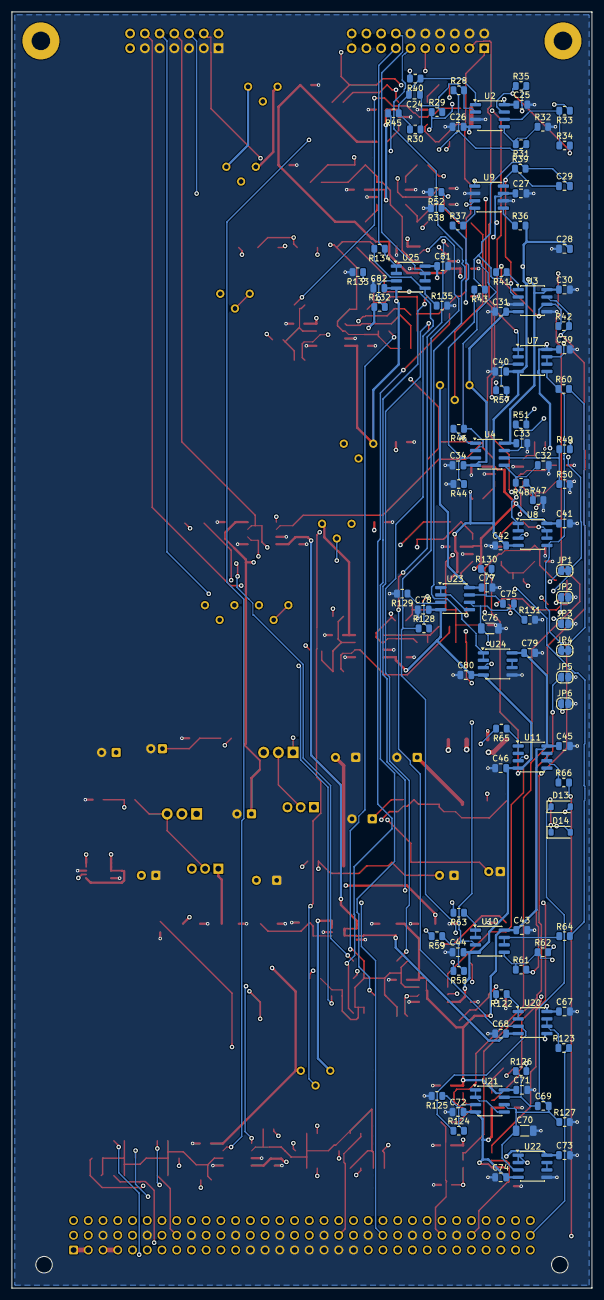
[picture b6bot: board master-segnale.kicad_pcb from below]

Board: 4 copper layers, 100.0 x 220.0 mm, 285 parts (106 on the bottom side), 161 nets.

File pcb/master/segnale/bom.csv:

quantita;valore;impronta;riferimenti;nota
2;220u 35V;CP_Radial_D8.0mm_P3.50mm;C1 C2;
1;4u7 25V;C_1206_3216Metric;C11;rumore del riferimento (datasheet: 4,7 uF)
3;4u7 25V;C_1206_3216Metric;C12 C14 C15;
2;10u 25V;C_1206_3216Metric;C13 C16;
1;1u;C_1206_3216Metric;C17;
52;100n;C_0805_2012Metric;C18 C19 C20 C21 C25 C26 C27 C28 C30 C31 C33 C34 C35 C36 C37 C38 C39 C40 C41 C42 C43 C44 C45 C46 C47 C48 C49 C50 C53 C54 C55 C56 C57 C58 C59 C60 C63 C64 C65 C66 C67 C68 C71 C72 C73 C74 C77 C78 C79 C80 C81 C82;
2;10p C0G;C_0805_2012Metric;C22 C23;
1;47p C0G;C_0805_2012Metric;C24;stesso polo dell'I/V del VCA (20k // 22p): separazione piatta fino a 20 kHz
5;22p C0G;C_0805_2012Metric;C29 C51 C52 C61 C62;
2;10u 35V;CP_Radial_D5.0mm_P2.00mm;C3 C7;
1;100n C0G;C_0805_2012Metric;C32;rampa 1 ms (dec. 80, senza BBM)
2;47u 35V;CP_Radial_D6.3mm_P2.50mm;C4 C8;
2;470u 25V;CP_Radial_D8.0mm_P3.50mm;C5 C9;
2;100u 25V;CP_Radial_D6.3mm_P2.50mm;C6 C10;
2;47p C0G;C_0805_2012Metric;C69 C75;
2;100n C0G;C_1206_3216Metric;C70 C76;hold: niente altro sul nodo (sim/meter)
1;1N4148W;D_SOD-123;D1;scarica Cadj
1;S1G;D_SMA;D2;protezione inversa
10;1N4148W;D_SOD-123;D3 D6 D7 D8 D9 D10 D11 D12 D13 D14;
1;S1G;D_SMA;D4;
1;LM4040-5.0;SOT-23;D5;
2;ferrite 600R;L_1206_3216Metric;FB1 FB2;
1;C96 maschio;DIN41612_C_3x32_Male_Horizontal_THT;J1;DIN 41612 C 3x32, angolo retto; a9-a12 sulle schede d'uscita (dec. 143)
1;2x7 cavo piatto;PinHeader_2x07_P2.54mm_Vertical;J2;NOTA: cavo piatto verso le schede di uscita affiancate (dec. 142); AGND fra i segnali
1;2x10 cavo piatto;PinHeader_2x10_P2.54mm_Vertical;J3;cavo piatto corto verso la scheda comandi (pot, MONO, meter); pin 17-20 liberi: +5V dalla J4 della scheda d'uscita L
1;BD139;TO-126-3_Vertical;Q40;
1;BD140;TO-126-3_Vertical;Q41;
2;120 1%;R_0805_2012Metric;R1 R4;
9;10k 0.1%;R_0805_2012Metric;R10 R11 R30 R32 R34 R87 R113 R132 R134;
1;43.2k 0.1%;R_0805_2012Metric;R106;
1;357k 0.1%;R_0805_2012Metric;R108;
1;20.0k 0.1%;R_0805_2012Metric;R109;
1;976 0.1%;R_0805_2012Metric;R111;
1;1.33k 0.1%;R_0805_2012Metric;R112;
33;20k 0.1%;R_0805_2012Metric;R12 R13 R14 R15 R16 R19 R20 R21 R22 R23 R24 R27 R28 R29 R31 R33 R35 R39 R40 R41 R42 R43 R44 R45 R46 R67 R71 R75 R76 R96 R100 R104 R105;
2;10k 0.1%;R_0805_2012Metric;R124 R128;g = 0,287 (FS +24 dBu -> 5,00 V; doc 0,288)
2;4k02 0.1%;R_0805_2012Metric;R125 R129;
2;3M;R_0805_2012Metric;R127 R131;release 0,3 s (dec. 81)
1;5k 0.1%;R_0805_2012Metric;R133;
1;4k64 0.1%;R_0805_2012Metric;R135;doc 4,625k: E96 4,64k = 1,585 V (+0,02 dB)
2;0;R_0805_2012Metric;R17 R25;MSUM6 (mic) dritto sul nodo: R di somma nei moduli (dec. 97)
2;0;R_0805_2012Metric;R18 R26;MSUM7 (mono) dritto sul nodo: R di somma nei moduli (dec. 97)
1;1k72 1%;R_0805_2012Metric;R2;19,2 V
1;1k;R_0805_2012Metric;R3;NOTA: cap-moltiplicatore come il FX-SEND (~150 mA qui)
5;6k19;R_0805_2012Metric;R36 R68 R72 R97 R101;NOTA: 5,1k del datasheet a -15 V riscalato a -18 V (2,4 mA)
5;150k;R_0805_2012Metric;R37 R69 R73 R98 R102;
5;51;R_0805_2012Metric;R38 R70 R74 R99 R103;
1;10k;R_0805_2012Metric;R47;NOTA: tasto a ritenuta verso +5 REF; aperto = stereo
1;10k;R_0805_2012Metric;R48;
1;10k2 0.1%;R_0805_2012Metric;R49;stadio della rampa x2,36: 5 V -> 11,8 V (todo 288)
1;1k72 1%;R_0805_2012Metric;R5;
1;7k5 0.1%;R_0805_2012Metric;R50;
3;18k2 0.1%;R_0805_2012Metric;R51 R91 R117;
1;1k 0.1%;R_0805_2012Metric;R52;11,8 V / 19,2 = 0,615 V = -100 dB; op-amp al rail: 0,80 V
1;47;R_0805_2012Metric;R53;NOTA: 47 ohm di uscita, stabilità sul cavo del backplane
7;47;R_0805_2012Metric;R54 R63 R64 R65 R66 R122 R123;
1;100k;R_0805_2012Metric;R55;ricevitore >= 100k; tiene l'ingresso senza ponticello
1;100k;R_0805_2012Metric;R56;
2;6k81 0.1%;R_0805_2012Metric;R57 R60;
2;3k16 0.1%;R_0805_2012Metric;R58 R61;
2;757 0.1%;R_0805_2012Metric;R59 R62;
3;1k;R_0805_2012Metric;R6 R126 R130;
2;150k 0.1%;R_0805_2012Metric;R7 R8;
2;68.1k 0.1%;R_0805_2012Metric;R77 R107;
1;137k 0.1%;R_0805_2012Metric;R78;ramo d'offset per il +6 dB (shaper-master.cir)
1;1.91k 0.1%;R_0805_2012Metric;R79;
2;2.43k 0.1%;R_0805_2012Metric;R80 R84;
1;16.9k 0.1%;R_0805_2012Metric;R81;
2;38.3k 0.1%;R_0805_2012Metric;R82 R110;
1;1.82k 0.1%;R_0805_2012Metric;R83;
1;1.96k 0.1%;R_0805_2012Metric;R85;
1;2.61k 0.1%;R_0805_2012Metric;R86;
2;9k76 0.1%;R_0805_2012Metric;R88 R114;
2;18k7 0.1%;R_0805_2012Metric;R89 R115;NOTA: stadio del partitore x(-1,916) e partitore 18,2k/1k: CV al pin = out/10,02; op-amp al rail = 0,8 V al pin (todo 281)
1;1k5;R_0805_2012Metric;R9;NOTA: ~6,7 mA nel riferimento
2;100k;R_0805_2012Metric;R90 R116;NOTA: pot staccato = shaper a 0 V = taglio massimo
4;1k 0.1%;R_0805_2012Metric;R92 R94 R118 R120;
2;17k4 0.1%;R_0805_2012Metric;R93 R119;
2;2M7;R_0805_2012Metric;R95 R121;
5;50k;Potentiometer_Bourns_3266W_Vertical;RV1 RV2 RV3 RV6 RV7;trim di simmetria (THD minima)
2;2k;Potentiometer_Bourns_3266W_Vertical;RV4 RV8;trim di law, 25 giri (vca-trim §3.2)
2;50k;Potentiometer_Bourns_3266W_Vertical;RV5 RV9;trim d'offset di coppia
2;OPA1612AIDR;SOIC-8_3.9x4.9mm_P1.27mm;U1 U20;
1;OPA1612AIDR;SOIC-8_3.9x4.9mm_P1.27mm;U10;[C] REC
1;OPA1612AIDR;SOIC-8_3.9x4.9mm_P1.27mm;U11;[N] MON verso il CUE
4;V2181L;SOIC-8_3.9x4.9mm_P1.27mm;U12 U13 U17 U18;
1;OPA1612AIDR;SOIC-8_3.9x4.9mm_P1.27mm;U14;I/V MASTER
1;OPA1612AIDR;SOIC-8_3.9x4.9mm_P1.27mm;U15;shaper M
1;OPA1612AIDR;SOIC-8_3.9x4.9mm_P1.27mm;U16;shaper B
1;OPA1612AIDR;SOIC-8_3.9x4.9mm_P1.27mm;U19;I/V BOOTH
1;OPA1612AIDR;SOIC-8_3.9x4.9mm_P1.27mm;U2;M e S
2;OPA1612AIDR;SOIC-8_3.9x4.9mm_P1.27mm;U21 U23;follower di scala e superdiodo
2;OPA1612AIDR;SOIC-8_3.9x4.9mm_P1.27mm;U22 U24;buffer dell'hold verso gli LM3915; seconda sezione libera, a inseguitore a massa
1;OPA1612AIDR;SOIC-8_3.9x4.9mm_P1.27mm;U25;vrefA 5,000 V e vrefB 1,58 V
1;OPA1612AIDR;SOIC-8_3.9x4.9mm_P1.27mm;U3;I/V del VCA di S e uscita R'
1;OPA1612AIDR;SOIC-8_3.9x4.9mm_P1.27mm;U30;+5 e -5 V di riferimento
1;OPA1612AIDR;SOIC-8_3.9x4.9mm_P1.27mm;U4;uscita L' e stadio della rampa MONO
1;LM317;TO-220-3_Vertical;U40;
1;LM337;TO-220-3_Vertical;U41;
1;LT3045EMSE;MSOP-12-1EP_3x4.039mm_P0.65mm_EP1.651x2.845mm;U42;EN/UV a IN; ILIM a massa = limite massimo; PG libero; PGFB a IN (fast start-up e PG spenti)
1;LT3094EMSE;MSOP-12-1EP_3x4.039mm_P0.65mm_EP1.651x2.845mm;U43;EN/UV a IN; PG libero; PGFB a IN (fast start-up e PG spenti); ILIM a massa; VIOC libero
1;OPA1612AIDR;SOIC-8_3.9x4.9mm_P1.27mm;U5;driver <= 50 ohm
1;OPA1612AIDR;SOIC-8_3.9x4.9mm_P1.27mm;U6;nodo di programma
1;OPA1612AIDR;SOIC-8_3.9x4.9mm_P1.27mm;U7;[A] verso MASTER LEVEL
1;OPA1612AIDR;SOIC-8_3.9x4.9mm_P1.27mm;U8;[B] verso BOOTH LEVEL
1;V2181L;SOIC-8_3.9x4.9mm_P1.27mm;U9;VCA del MONO: 0 dB a tasto spento, -100 dB a tasto premuto
